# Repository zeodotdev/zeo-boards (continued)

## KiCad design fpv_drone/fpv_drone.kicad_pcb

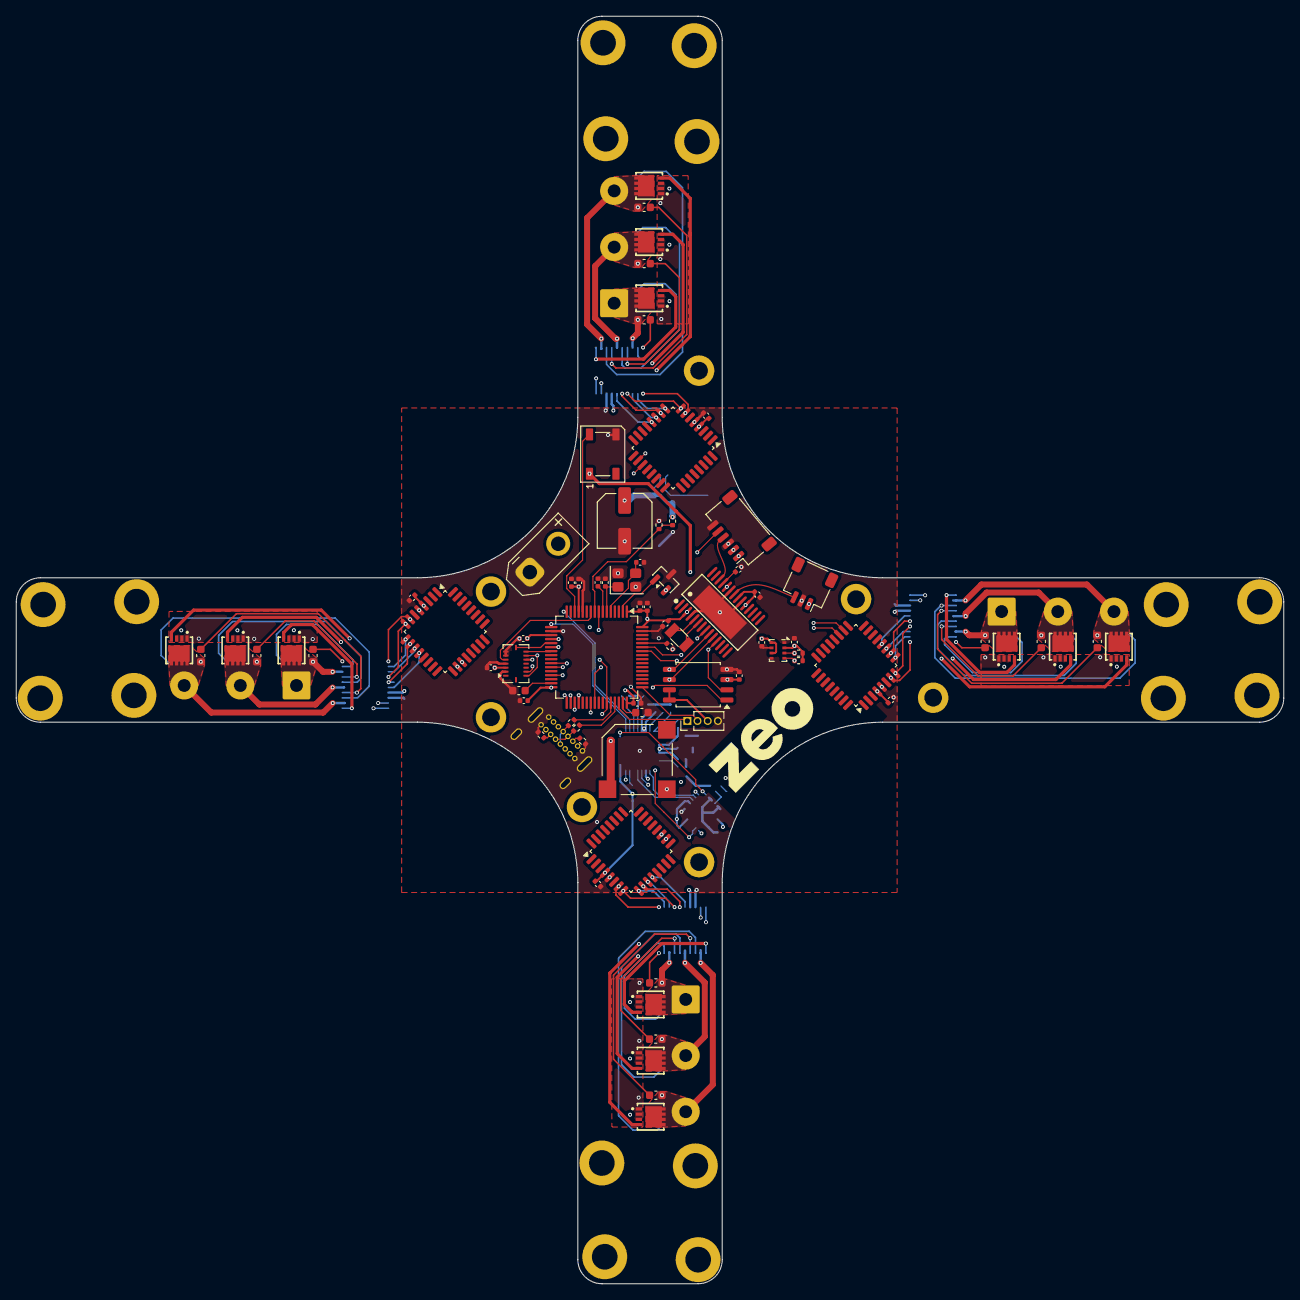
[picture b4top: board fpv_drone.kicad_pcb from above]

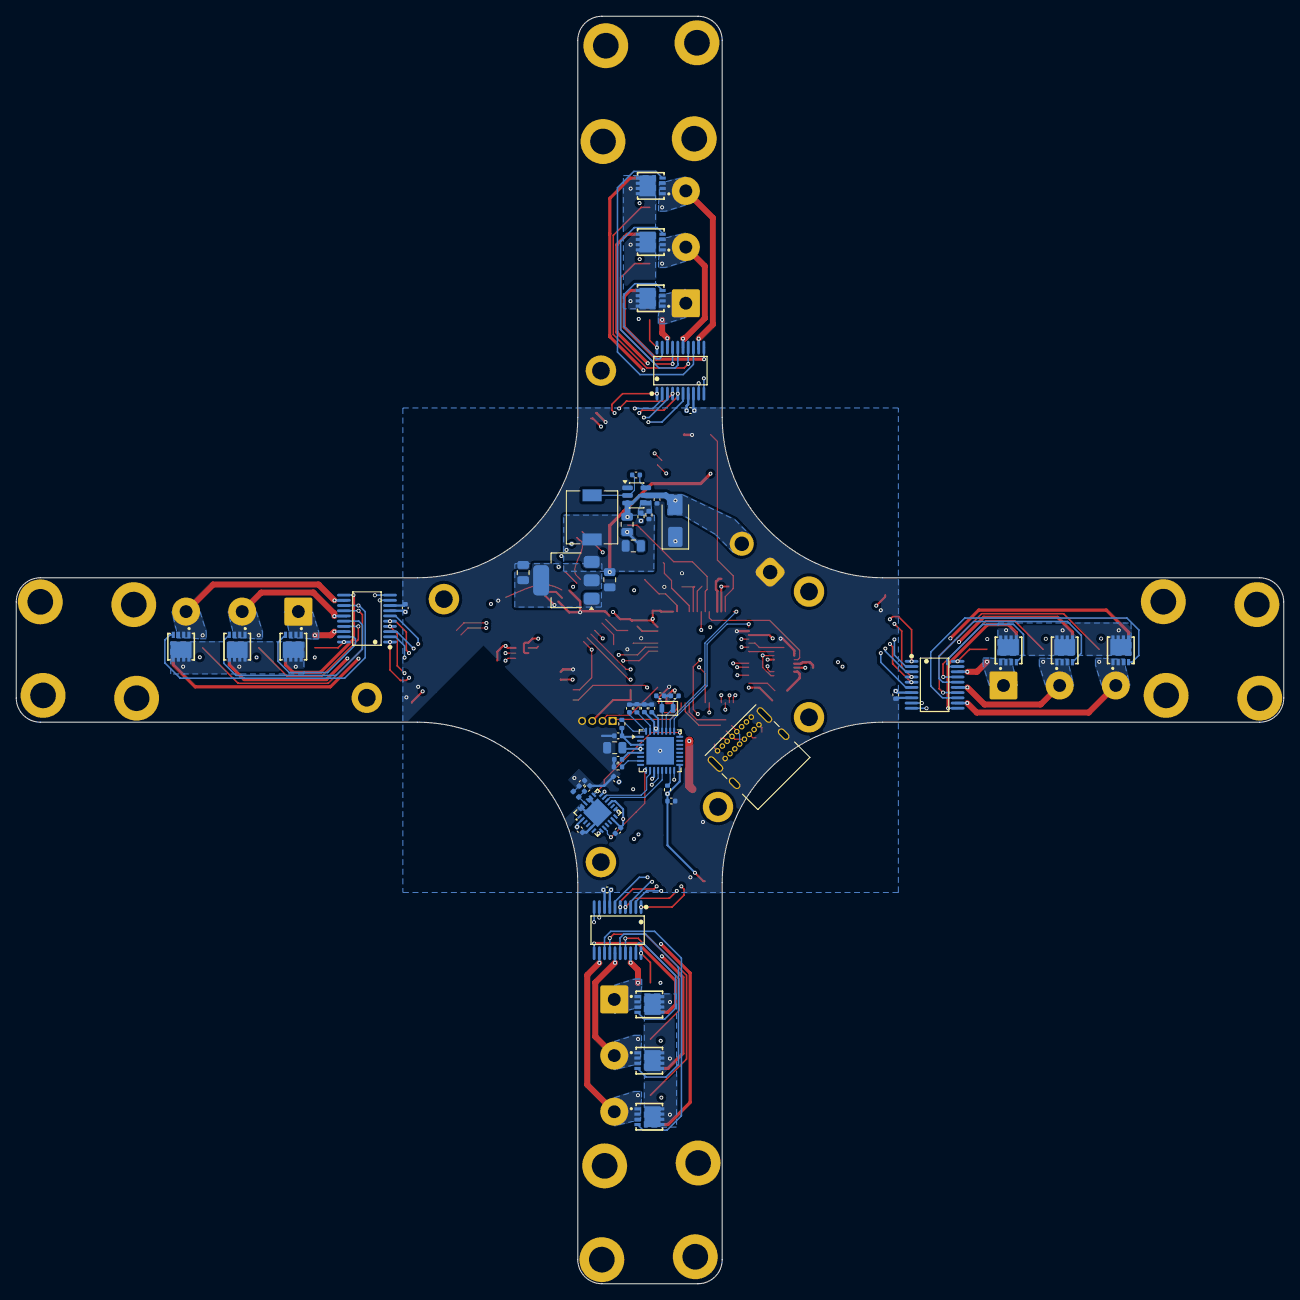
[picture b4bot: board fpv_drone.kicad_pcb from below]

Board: 6 copper layers, 158.0 x 158.0 mm, 134 parts (55 on the bottom side), 135 nets.

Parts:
C1, C60: DNP; C_0402_1005Metric
C2: 470µF/25V; C_Elec_6.3x5.8
C3, C11, C58: 10µF; C_0805_2012Metric
C4, C5, C6, C7, C8, C13, C14, C15, C19, C20, C21, C22, C23, C24, C25, C28, C31, C32, C33, C34, C38, C39, C43, C44, C48, C49, C53, C54, C55, C56, C57, C59: 100nF; C_0402_1005Metric
C9, C12: 22µF; C_0805_2012Metric
C10, C18: 1µF; C_0402_1005Metric
C16, C17: 10pF; C_0402_1005Metric
C26, C27: 20pF; C_0402_1005Metric
C29, C30: 2.2µF; C_0603_1608Metric
C35, C36, C37, C40, C41, C42, C45, C46, C47, C50, C51, C52: 100nF; C_0603_1608Metric
D2: SMBJ20A; D_SMA
D3: WS2812B; LED_WS2812B_PLCC4_5.0x5.0mm_P3.2mm
J2: BATT; AMASS_XT30UPB-M_1x02_P5.0mm_Vertical
J4: CAM; JST_SH_SM03B-SRSS-TB_1x03-1MP_P1.00mm_Horizontal
J5: VTX_MODULE; JST_SH_SM06B-SRSS-TB_1x06-1MP_P1.00mm_Horizontal
J6: USB-C; USB_C_Receptacle_GCT_USB4085
J7: MOT1; SolderWire-0.75sqmm_1x03_P7mm_D1.25mm_OD3.5mm
J8, J9, J10: MOT3; SolderWire-0.75sqmm_1x03_P7mm_D1.25mm_OD3.5mm
J11: BUZZER; MagneticBuzzer_Kobitone_254-EMB84Q-RO
J12: SWD_DEBUG; PinHeader_1x04_P1.27mm_Vertical
L1: 1.5nH; L_0402_1005Metric
L2: 4.7µH; L_6.3x6.3_H3
Q1, Q2, Q3, Q4, Q5, Q6, Q7, Q8, Q9, Q10, Q11, Q12, Q13, Q14, Q15, Q16, Q17, Q18, Q19, Q20, Q21, Q22, Q23, Q24: AON7418; PDFN-8_L3.3-W3.3-P0.65-BL
Q26: BSS138; SOT-23
R2: 73.2k; R_0402_1005Metric
R3, R7, R8, R9, R10: 10k; R_0402_1005Metric
R6: 12k; R_0402_1005Metric
R11, R12: 5.1k; R_0402_1005Metric
R13, R14: 22; R_0402_1005Metric
R15, R16: 100k; R_0402_1005Metric
R17, R18: 4.7k; R_0402_1005Metric
U2: TPS54302_5V; SOT-23-6
U4: AMS1117-3.3; SOT-223-3_TabPin2
U5: SX1280; QFN-24_L4.0-W4.0-P0.50-BL-EP2.6
U6: ESP8266EX; QFN-32-1EP_5x5mm_P0.5mm_EP3.45x3.45mm
U7: AT7456E; TSSOP-28_L9.7-W4.4-P0.65-LS6.4-BL-EP-2
U8: STM32F405RGTx; LQFP-64_10x10mm_P0.5mm
U9: STM32G071K_ESC1; LQFP-32_7x7mm_P0.8mm
U10: FD6288_ESC1; TSSOP-20_L6.5-W4.4-P0.65-LS6.4-BL
U11: STM32G071K_ESC3; LQFP-32_7x7mm_P0.8mm
U12: FD6288_ESC3; TSSOP-20_L6.5-W4.4-P0.65-LS6.4-BL
U13: STM32G071K_ESC2; LQFP-32_7x7mm_P0.8mm
U14: FD6288_ESC2; TSSOP-20_L6.5-W4.4-P0.65-LS6.4-BL
U15: STM32G071K_ESC4; LQFP-32_7x7mm_P0.8mm
U16: FD6288_ESC4; TSSOP-20_L6.5-W4.4-P0.65-LS6.4-BL
U17: BMI088; Bosch_LGA-16_4.5x3mm_P0.5mm_LayoutBorder7x1y_ClockwisePinNu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
U18: BMP280; Bosch_LGA-8_2x2.5mm_P0.65mm_ClockwisePinNumbering
U19: W25Q128JVS; SOIC-8_5.3x5.3mm_P1.27mm
Y2: 26MHz; Crystal_SMD_2012-2Pin_2.0x1.2mm
Y3: 27MHz; Crystal_SMD_3215-2Pin_3.2x1.5mm
Y4: 8MHz; Crystal_SMD_3225-4Pin_3.2x2.5mm

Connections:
+3V3: C5.2, C6.2, C7.2, C10.2, C12.2, C13.2, C14.2, C15.2, C19.2, C20.2, C21.2, C22.2, C23.2, C25.2, C31.2, C32.2, C33.2, C38.2, C43.2, C48.2, C53.1, C54.2, C55.2, C56.2, C57.2, C58.2, C59.2, J12.3, R7.2, R9.2, R17.2, R18.2, U4.2 (VO), U5.2 (VDD_IN), U5.11 (VBAT_IO), U5.15 (VBAT), U6.1 (VDDA), U6.3 (VDD3P3), U6.4 (VDD3P3), U6.5 (VDD_RTC), U6.11 (VDDPST), U6.17 (VDDPST), U6.29 (VDDD), U6.30 (VDDA), U7.3 (DVDD), U7.19 (RESET#), U7.21 (AVDD), U8.1 (VBAT), U8.13 (VDDA), U8.19 (VDD), U8.32 (VDD), U8.48 (VDD), U8.64 (VDD), U9.4 (VDD), U11.4 (VDD), U13.4 (VDD), U15.4 (VDD), U17.3 (VDD), U17.11 (VDDIO), U18.2 (CSB), U18.6 (VDDIO), U18.8 (VDD), U19.3 (~WP/IO_{2}), U19.7 (~HOLD/~RESET/IO_{3}), U19.8 (VCC)
+5V: C9.2, C11.2, D3.1 (VDD), J4.1, J5.1, J5.2, J11.1, L2.1, R2.2, U4.3 (VI), U7.24 (PVDD)
+BATT: C2.1, C3.2, C4.1, C34.2, C39.2, C44.2, C49.2, D2.2 (A2), J2.2, Q1.5 (D), Q1.6 (D), Q1.7 (D), Q1.8 (D), Q1.9 (D), Q3.5 (D), Q3.6 (D), Q3.7 (D), Q3.8 (D), Q3.9 (D), Q5.5 (D), Q5.6 (D), Q5.7 (D), Q5.8 (D), Q5.9 (D), Q7.5 (D), Q7.6 (D), Q7.7 (D), Q7.8 (D), Q7.9 (D), Q9.5 (D), Q9.6 (D), Q9.7 (D), Q9.8 (D), Q9.9 (D), Q11.5 (D), Q11.6 (D), Q11.7 (D), Q11.8 (D), Q11.9 (D), Q13.5 (D), Q13.6 (D), Q13.7 (D), Q13.8 (D), Q13.9 (D), Q15.5 (D), Q15.6 (D), Q15.7 (D), Q15.8 (D), Q15.9 (D), Q17.5 (D), Q17.6 (D), Q17.7 (D), Q17.8 (D), Q17.9 (D), Q19.5 (D), Q19.6 (D), Q19.7 (D), Q19.8 (D), Q19.9 (D), Q21.5 (D), Q21.6 (D), Q21.7 (D), Q21.8 (D), Q21.9 (D), Q23.5 (D), Q23.6 (D), Q23.7 (D), Q23.8 (D), Q23.9 (D), R15.1, U2.3 (VIN), U2.5 (EN), U10.7 (VCC), U12.7 (VCC), U14.7 (VCC), U16.7 (VCC)
/BARO_SCL: R17.1, U8.58 (PB6), U18.4 (SCK)
/BARO_SDA: R18.1, U8.59 (PB7), U18.3 (SDI)
/BUZZER: Q26.1 (G), U8.2 (PC13)
/ELRS Receiver/SX_BUSY: U5.7 (BUSY), U6.16 (GPIO4)
/ELRS Receiver/SX_DIO1: U5.8 (DIO1), U6.9 (MTMS)
/ELRS Receiver/SX_MISO: U5.16 (MISO_TX), U6.13 (MTDO)
/ELRS Receiver/SX_MOSI: U5.17 (MOSI_RX), U6.10 (MTDI)
/ELRS Receiver/SX_NSS: U5.19 (NSS_CTS), U6.24 (GPIO5)
/ELRS Receiver/SX_SCK: U5.18 (SCK_RTSN), U6.12 (MTCK)
/ELRS_RX: U6.25 (U0RXD), U8.17 (PA3)
/ELRS_TX: U6.26 (U0TXD), U8.16 (PA2)
/ESC/Motor 1/HIN1: U9.7 (PA0), U10.1 (HIN1)
/ESC/Motor 1/HIN2: U9.9 (PA2), U10.2 (HIN2)
/ESC/Motor 1/HIN3: U9.11 (PA4), U10.3 (HIN3)
/ESC/Motor 1/HO1: Q1.4 (G), U10.19 (HO1)
/ESC/Motor 1/HO2: Q3.4 (G), U10.16 (HO2)
/ESC/Motor 1/HO3: Q5.4 (G), U10.13 (HO3)
/ESC/Motor 1/LIN1: U9.8 (PA1), U10.4 (LIN1)
/ESC/Motor 1/LIN2: U9.10 (PA3), U10.5 (LIN2)
/ESC/Motor 1/LIN3: U9.12 (PA5), U10.6 (LIN3)
/ESC/Motor 1/LO1: Q2.4 (G), U10.11 (LO1)
/ESC/Motor 1/LO2: Q4.4 (G), U10.10 (LO2)
/ESC/Motor 1/LO3: Q6.4 (G), U10.9 (LO3)
/ESC/Motor 1/VB1: C35.1, U10.20 (VB1)
/ESC/Motor 1/VB2: C36.1, U10.17 (VB2)
/ESC/Motor 1/VB3: C37.1, U10.14 (VB3)
/ESC/Motor 1/VS1: C35.2, J7.1, Q1.1 (S), Q1.2 (S), Q1.3 (S), Q2.5 (D), Q2.6 (D), Q2.7 (D), Q2.8 (D), Q2.9 (D), U10.18 (VS1)
/ESC/Motor 1/VS2: C36.2, J7.2, Q3.1 (S), Q3.2 (S), Q3.3 (S), Q4.5 (D), Q4.6 (D), Q4.7 (D), Q4.8 (D), Q4.9 (D), U10.15 (VS2)
/ESC/Motor 1/VS3: C37.2, J7.3, Q5.1 (S), Q5.2 (S), Q5.3 (S), Q6.5 (D), Q6.6 (D), Q6.7 (D), Q6.8 (D), Q6.9 (D), U10.12 (VS3)
/ESC/Motor 2/HIN1: U13.7 (PA0), U14.1 (HIN1)
/ESC/Motor 2/HIN2: U13.9 (PA2), U14.2 (HIN2)
/ESC/Motor 2/HIN3: U13.11 (PA4), U14.3 (HIN3)
/ESC/Motor 2/HO1: Q13.4 (G), U14.19 (HO1)
/ESC/Motor 2/HO2: Q15.4 (G), U14.16 (HO2)
/ESC/Motor 2/HO3: Q17.4 (G), U14.13 (HO3)
/ESC/Motor 2/LIN1: U13.8 (PA1), U14.4 (LIN1)
/ESC/Motor 2/LIN2: U13.10 (PA3), U14.5 (LIN2)
/ESC/Motor 2/LIN3: U13.12 (PA5), U14.6 (LIN3)
/ESC/Motor 2/LO1: Q14.4 (G), U14.11 (LO1)
/ESC/Motor 2/LO2: Q16.4 (G), U14.10 (LO2)
/ESC/Motor 2/LO3: Q18.4 (G), U14.9 (LO3)
/ESC/Motor 2/VB1: C45.1, U14.20 (VB1)
/ESC/Motor 2/VB2: C46.1, U14.17 (VB2)
/ESC/Motor 2/VB3: C47.1, U14.14 (VB3)
/ESC/Motor 2/VS1: C45.2, J9.1, Q13.1 (S), Q13.2 (S), Q13.3 (S), Q14.5 (D), Q14.6 (D), Q14.7 (D), Q14.8 (D), Q14.9 (D), U14.18 (VS1)
/ESC/Motor 2/VS2: C46.2, J9.2, Q15.1 (S), Q15.2 (S), Q15.3 (S), Q16.5 (D), Q16.6 (D), Q16.7 (D), Q16.8 (D), Q16.9 (D), U14.15 (VS2)
/ESC/Motor 2/VS3: C47.2, J9.3, Q17.1 (S), Q17.2 (S), Q17.3 (S), Q18.5 (D), Q18.6 (D), Q18.7 (D), Q18.8 (D), Q18.9 (D), U14.12 (VS3)
/ESC/Motor 3/HIN1: U11.7 (PA0), U12.1 (HIN1)
/ESC/Motor 3/HIN2: U11.9 (PA2), U12.2 (HIN2)
/ESC/Motor 3/HIN3: U11.11 (PA4), U12.3 (HIN3)
/ESC/Motor 3/HO1: Q7.4 (G), U12.19 (HO1)
/ESC/Motor 3/HO2: Q9.4 (G), U12.16 (HO2)
/ESC/Motor 3/HO3: Q11.4 (G), U12.13 (HO3)
/ESC/Motor 3/LIN1: U11.8 (PA1), U12.4 (LIN1)
/ESC/Motor 3/LIN2: U11.10 (PA3), U12.5 (LIN2)
/ESC/Motor 3/LIN3: U11.12 (PA5), U12.6 (LIN3)
/ESC/Motor 3/LO1: Q8.4 (G), U12.11 (LO1)
/ESC/Motor 3/LO2: Q10.4 (G), U12.10 (LO2)
/ESC/Motor 3/LO3: Q12.4 (G), U12.9 (LO3)
/ESC/Motor 3/VB1: C40.1, U12.20 (VB1)
/ESC/Motor 3/VB2: C41.1, U12.17 (VB2)
/ESC/Motor 3/VB3: C42.1, U12.14 (VB3)
/ESC/Motor 3/VS1: C40.2, J8.1, Q7.1 (S), Q7.2 (S), Q7.3 (S), Q8.5 (D), Q8.6 (D), Q8.7 (D), Q8.8 (D), Q8.9 (D), U12.18 (VS1)
/ESC/Motor 3/VS2: C41.2, J8.2, Q9.1 (S), Q9.2 (S), Q9.3 (S), Q10.5 (D), Q10.6 (D), Q10.7 (D), Q10.8 (D), Q10.9 (D), U12.15 (VS2)
/ESC/Motor 3/VS3: C42.2, J8.3, Q11.1 (S), Q11.2 (S), Q11.3 (S), Q12.5 (D), Q12.6 (D), Q12.7 (D), Q12.8 (D), Q12.9 (D), U12.12 (VS3)
/ESC/Motor 4/HIN1: U15.7 (PA0), U16.1 (HIN1)
/ESC/Motor 4/HIN2: U15.9 (PA2), U16.2 (HIN2)
/ESC/Motor 4/HIN3: U15.11 (PA4), U16.3 (HIN3)
/ESC/Motor 4/HO1: Q19.4 (G), U16.19 (HO1)
/ESC/Motor 4/HO2: Q21.4 (G), U16.16 (HO2)
/ESC/Motor 4/HO3: Q23.4 (G), U16.13 (HO3)
/ESC/Motor 4/LIN1: U15.8 (PA1), U16.4 (LIN1)
/ESC/Motor 4/LIN2: U15.10 (PA3), U16.5 (LIN2)
/ESC/Motor 4/LIN3: U15.12 (PA5), U16.6 (LIN3)
/ESC/Motor 4/LO1: Q20.4 (G), U16.11 (LO1)
/ESC/Motor 4/LO2: Q22.4 (G), U16.10 (LO2)
/ESC/Motor 4/LO3: Q24.4 (G), U16.9 (LO3)
/ESC/Motor 4/VB1: C50.1, U16.20 (VB1)
/ESC/Motor 4/VB2: C51.1, U16.17 (VB2)
/ESC/Motor 4/VB3: C52.1, U16.14 (VB3)
/ESC/Motor 4/VS1: C50.2, J10.1, Q19.1 (S), Q19.2 (S), Q19.3 (S), Q20.5 (D), Q20.6 (D), Q20.7 (D), Q20.8 (D), Q20.9 (D), U16.18 (VS1)
/ESC/Motor 4/VS2: C51.2, J10.2, Q21.1 (S), Q21.2 (S), Q21.3 (S), Q22.5 (D), Q22.6 (D), Q22.7 (D), Q22.8 (D), Q22.9 (D), U16.15 (VS2)
/ESC/Motor 4/VS3: C52.2, J10.3, Q23.1 (S), Q23.2 (S), Q23.3 (S), Q24.5 (D), Q24.6 (D), Q24.7 (D), Q24.8 (D), Q24.9 (D), U16.12 (VS3)
/ESC_RX: U8.43 (PA10), U9.18 (PA8), U11.18 (PA8), U13.18 (PA8), U15.18 (PA8)
/FLASH_CS: U8.8 (PC0), U19.1 (~CS)
/Flight Controller/USB_DM: R13.1, U8.44 (PA11)
/Flight Controller/USB_DP: R14.1, U8.45 (PA12)
/IMU_ACC_CS: U8.10 (PC2), U17.5 (~CSB2)
/IMU_CS: U8.20 (PA4), U17.14 (~CSB1)
/IMU_MISO: U8.22 (PA6), U17.10 (SDO2), U17.15 (SDO1)
/IMU_MOSI: U8.23 (PA7), U17.9 (SDI/SDA)
/IMU_SCK: U8.21 (PA5), U17.8 (SCK/SCL)
/LED_DATA: D3.4 (DIN), U8.14 (PA0)
/MOT1_PWM: U8.26 (PB0), U9.19 (PA9/UCPD1_DBCC1)
/MOT2_PWM: U8.27 (PB1), U13.19 (PA9/UCPD1_DBCC1)
/MOT3_PWM: U8.39 (PC8), U11.19 (PA9/UCPD1_DBCC1)
/MOT4_PWM: U8.40 (PC9), U15.19 (PA9/UCPD1_DBCC1)
/OSD and VTX/VID_IN: J4.3, U7.22 (VIN)
/OSD and VTX/VID_OUT: J5.4, U7.26 (VOUT)
/OSD_CS: U7.8 (CS#), U8.33 (PB12)
/Power Supply/FB_5V: R2.1, R3.2, U2.4 (FB)
/Power Supply/SW_5V: C8.2, L2.2, U2.2 (SW)
/SPI2_MISO: U7.11 (SDOUT), U8.35 (PB14), U19.2 (DO/IO_{1})
/SPI2_MOSI: U7.9 (SDIN), U8.36 (PB15), U19.5 (DI/IO_{0})
/SPI2_SCK: U7.10 (SCLK), U8.34 (PB13), U19.6 (CLK)
/SWCLK: J12.2, U8.49 (PA14)
/SWDIO: J12.1, U8.46 (PA13)
/VBAT_SENSE: R15.2, R16.1, U8.9 (PC1)
/VTX_SA: J5.5, U8.29 (PB10)
GND: C1.2, C2.2, C3.1, C4.2, C5.1, C6.1, C7.1, C9.1, C10.1, C11.1, C12.1, C13.1, C14.1, C15.1, C16.1, C17.2, C18.1, C19.1, C20.1, C21.1, C22.1, C23.1, C24.2, C25.1, C26.2, C27.1, C28.1, C29.1, C30.1, C31.1, C32.1, C33.1, C34.1, C38.1, C39.1, C43.1, C44.1, C48.1, C49.1, C53.2, C54.1, C55.1, C56.1, C57.1, C58.1, C59.1, C60.1, C60.2, D2.1 (A1), D3.3 (VSS), J2.1, J4.2, J5.3, J5.6, J6.A1 (GND), J6.A12 (GND), J6.B1 (GND), J6.B12 (GND), J6.S1 (SHIELD), J12.4, L1.2, Q2.1 (S), Q2.2 (S), Q2.3 (S), Q4.1 (S), Q4.2 (S), Q4.3 (S), Q6.1 (S), Q6.2 (S), Q6.3 (S), Q8.1 (S), Q8.2 (S), Q8.3 (S), Q10.1 (S), Q10.2 (S), Q10.3 (S), Q12.1 (S), Q12.2 (S), Q12.3 (S), Q14.1 (S), Q14.2 (S), Q14.3 (S), Q16.1 (S), Q16.2 (S), Q16.3 (S), Q18.1 (S), Q18.2 (S), Q18.3 (S), Q20.1 (S), Q20.2 (S), Q20.3 (S), Q22.1 (S), Q22.2 (S), Q22.3 (S), Q24.1 (S), Q24.2 (S), Q24.3 (S), Q26.3 (S), R3.1, R6.1, R8.2, R10.1, R11.1, R12.1, R16.2, U2.1 (GND), U4.1 (GND), U5.5 (GND), U5.13 (GND), U5.20 (GND), U5.21 (GND), U5.23 (GND), U5.24 (GND), U5.25 (GND), U6.33 (GND), U7.4 (DGND), U7.20 (AGND), U7.23 (PGND), U7.29 (EP), U8.12 (VSSA), U8.18 (VSS), U8.63 (VSS), U9.5 (VSS), U10.8 (COM), U11.5 (VSS), U12.8 (COM), U13.5 (VSS), U14.8 (COM), U15.5 (VSS), U16.8 (COM), U17.2 (GNDA), U17.4 (GNDA), U17.6 (GNDIO), U17.7 (PS), U18.1 (GND), U18.5 (SDO), U18.7 (GND), U19.4 (GND), Y4.2 (G), Y4.4 (G)
unnamed: J6.A5 (CC1), R11.2
unnamed: J6.B5 (CC2), R12.2
unnamed: J6.A6 (D+), J6.B6 (D+), R14.2
unnamed: J6.A7 (D-), J6.B7 (D-), R13.2
unnamed: J11.2, Q26.2 (D)
unnamed: C8.1, U2.6 (BOOT)
unnamed: C1.1, L1.1, U5.22 (RFIO)
unnamed: R8.1, U6.7 (CHIP_PU)
unnamed: R9.1, U6.15 (GPIO0)
unnamed: R6.2, U6.31 (RES12K)
unnamed: C17.1, U6.28 (XTAL_IN), Y2.2
unnamed: C16.2, U6.27 (XTAL_OUT), Y2.1
unnamed: C18.2, R7.1, U6.32 (~EXT_RSTB)
unnamed: U7.5 (CLKIN), Y3.2
unnamed: C24.1, U7.25 (SAG)
unnamed: U7.6 (XFB), Y3.1
unnamed: R10.2, U8.60 (BOOT0)
unnamed: C28.2, U8.7 (NRST)
unnamed: C26.1, U8.5 (PH0), Y4.3
unnamed: C27.2, U8.6 (PH1), Y4.1
unnamed: C29.2, U8.31 (VCAP_1)
unnamed: C30.2, U8.47 (VCAP_2)

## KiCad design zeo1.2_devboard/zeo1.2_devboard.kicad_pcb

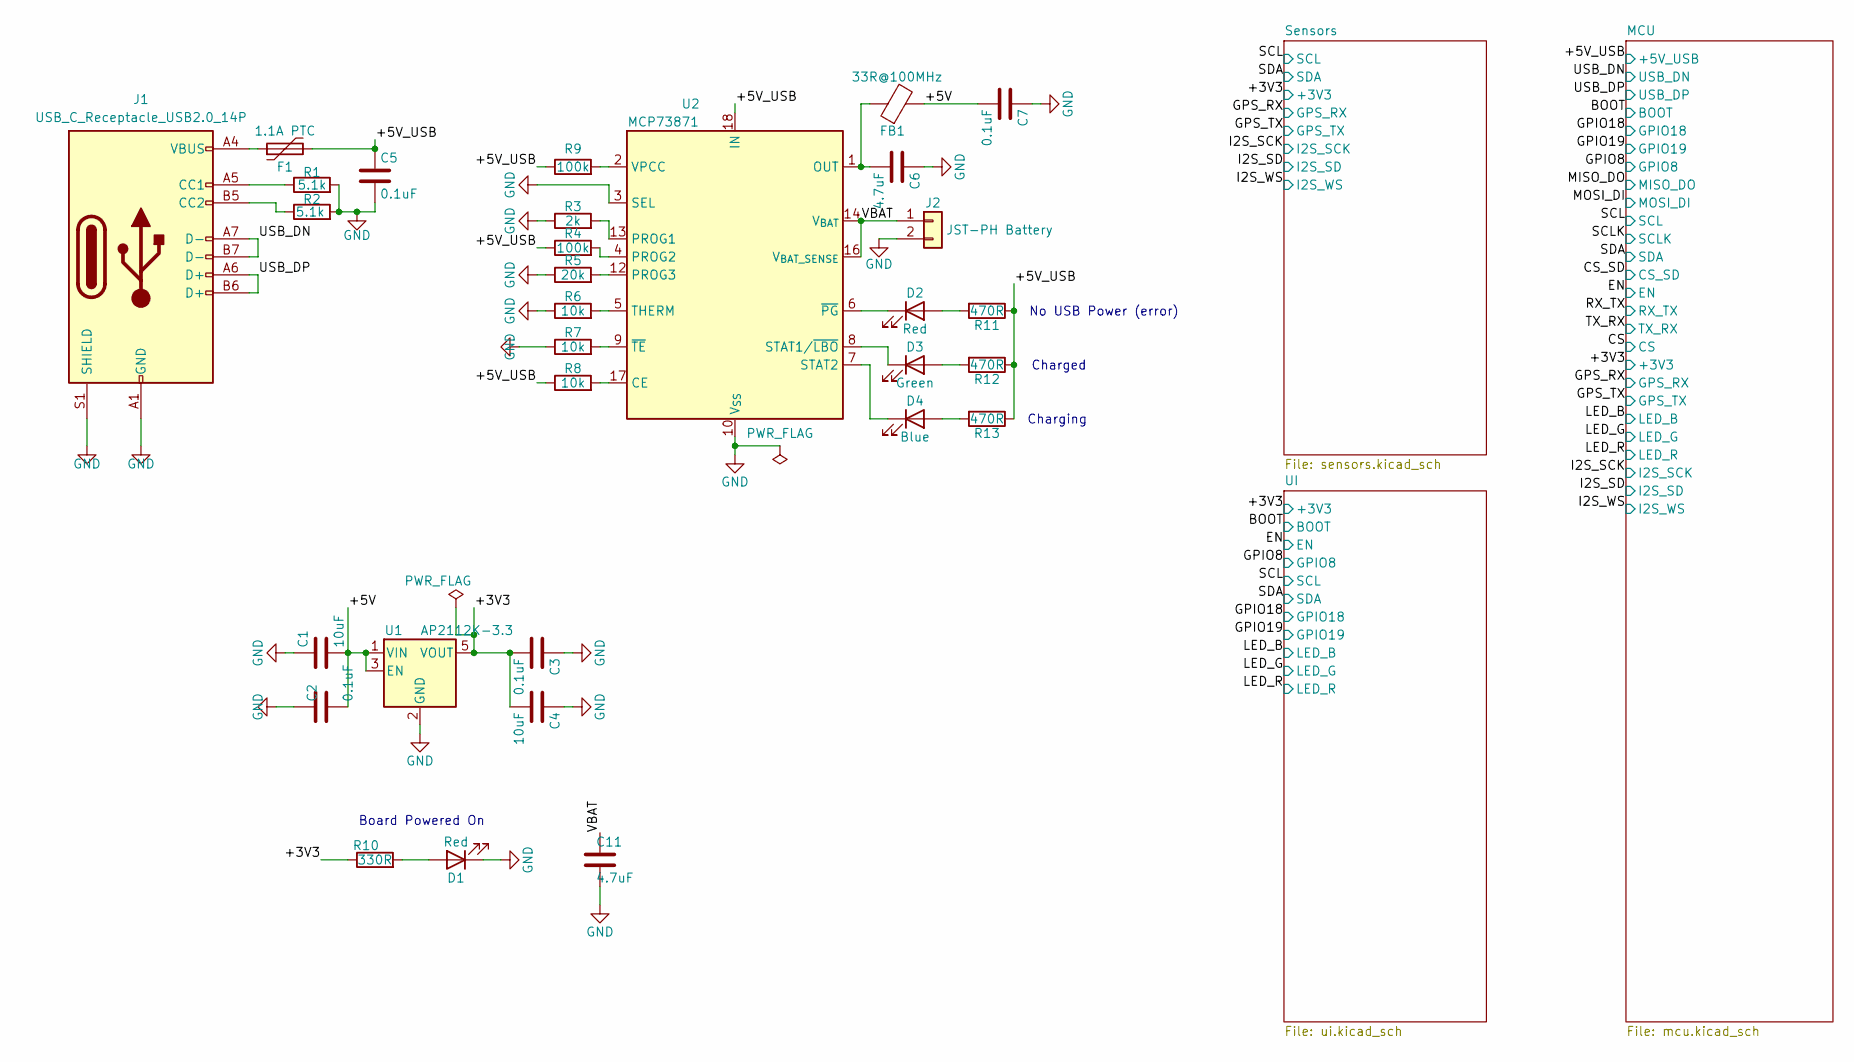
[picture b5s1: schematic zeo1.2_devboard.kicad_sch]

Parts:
C1, C4: 10uF; C_0805_2012Metric
C2, C3, C5, C7: 0.1uF; C_0402_1005Metric
C6: 4.7uF; C_0402_1005Metric
C11: 4.7uF; C_0805_2012Metric
D1, D2: Red; LED_0402_1005Metric
D3: Green; LED_0402_1005Metric
D4: Blue; LED_0402_1005Metric
F1: 1.1A PTC; Fuse_0402_1005Metric
FB1: 33R@100MHz; L_0402_1005Metric
J1: USB_C_Receptacle_USB2.0_14P; USB_C_Receptacle_GCT_USB4085
J2: JST-PH Battery; JST_PH_B2B-PH-K_1x02_P2.00mm_Vertical
R1, R2: 5.1k; R_0402_1005Metric
R3: 2k; R_0402_1005Metric
R4, R9: 100k; R_0402_1005Metric
R5: 20k; R_0402_1005Metric
R6, R7, R8: 10k; R_0402_1005Metric
R10: 330R; R_0402_1005Metric
R11, R12, R13: 470R; R_0402_1005Metric
U1: AP2112K-3.3; SOT-23-5
U2: MCP73871; QFN-20-1EP_4x4mm_P0.5mm_EP2.5x2.5mm

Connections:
+3V3: C3.2, C4.2, R10.1, U1.5 (VOUT); also elsewhere on the board
/+5V: C1.2, C2.2, C7.2, FB1.2, U1.1 (VIN), U1.3 (EN)
/+5V_USB: C5.1, F1.2, R4.1, R8.1, R9.1, R11.1, R12.1, R13.1, U2.18 (IN), U2.19 (IN); also elsewhere on the board
/USB_DN: J1.A7 (D-), J1.B7 (D-); also elsewhere on the board
/USB_DP: J1.A6 (D+), J1.B6 (D+); also elsewhere on the board
/VBAT: C11.1, J2.1, U2.14 (V_{BAT}), U2.15 (V_{BAT}), U2.16 (V_{BAT_SENSE})
GND: C1.1, C2.1, C3.1, C4.1, C5.2, C6.1, C7.1, C11.2, D1.1 (K), J1.A1 (GND), J1.A12 (GND), J1.B1 (GND), J1.B12 (GND), J1.S1 (SHIELD), J2.2, R1.2, R2.2, R3.1, R5.1, R6.1, R7.1, U1.2 (GND), U2.3 (SEL), U2.10 (V_{SS}), U2.11 (V_{SS}), U2.21 (V_{SS}); also elsewhere on the board
unnamed: C6.2, FB1.1, U2.1 (OUT), U2.20 (OUT)
unnamed: D1.2 (A), R10.2
unnamed: D2.2 (A), R11.2
unnamed: D2.1 (K), U2.6 (~PG)
unnamed: D3.2 (A), R12.2
unnamed: D3.1 (K), U2.8 (STAT1/~LBO)
unnamed: D4.2 (A), R13.2
unnamed: D4.1 (K), U2.7 (STAT2)
unnamed: F1.1, J1.A4 (VBUS), J1.A9 (VBUS), J1.B4 (VBUS), J1.B9 (VBUS)
unnamed: J1.A5 (CC1), R1.1
unnamed: J1.B5 (CC2), R2.1
unnamed: R8.2, U2.17 (CE)
unnamed: R3.2, U2.13 (PROG1)
unnamed: R4.2, U2.4 (PROG2)
unnamed: R5.2, U2.12 (PROG3)
unnamed: R6.2, U2.5 (THERM)
unnamed: R9.2, U2.2 (VPCC)
unnamed: R7.2, U2.9 (~TE)

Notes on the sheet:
Charged
Board Powered On
Charging
No USB Power (error)

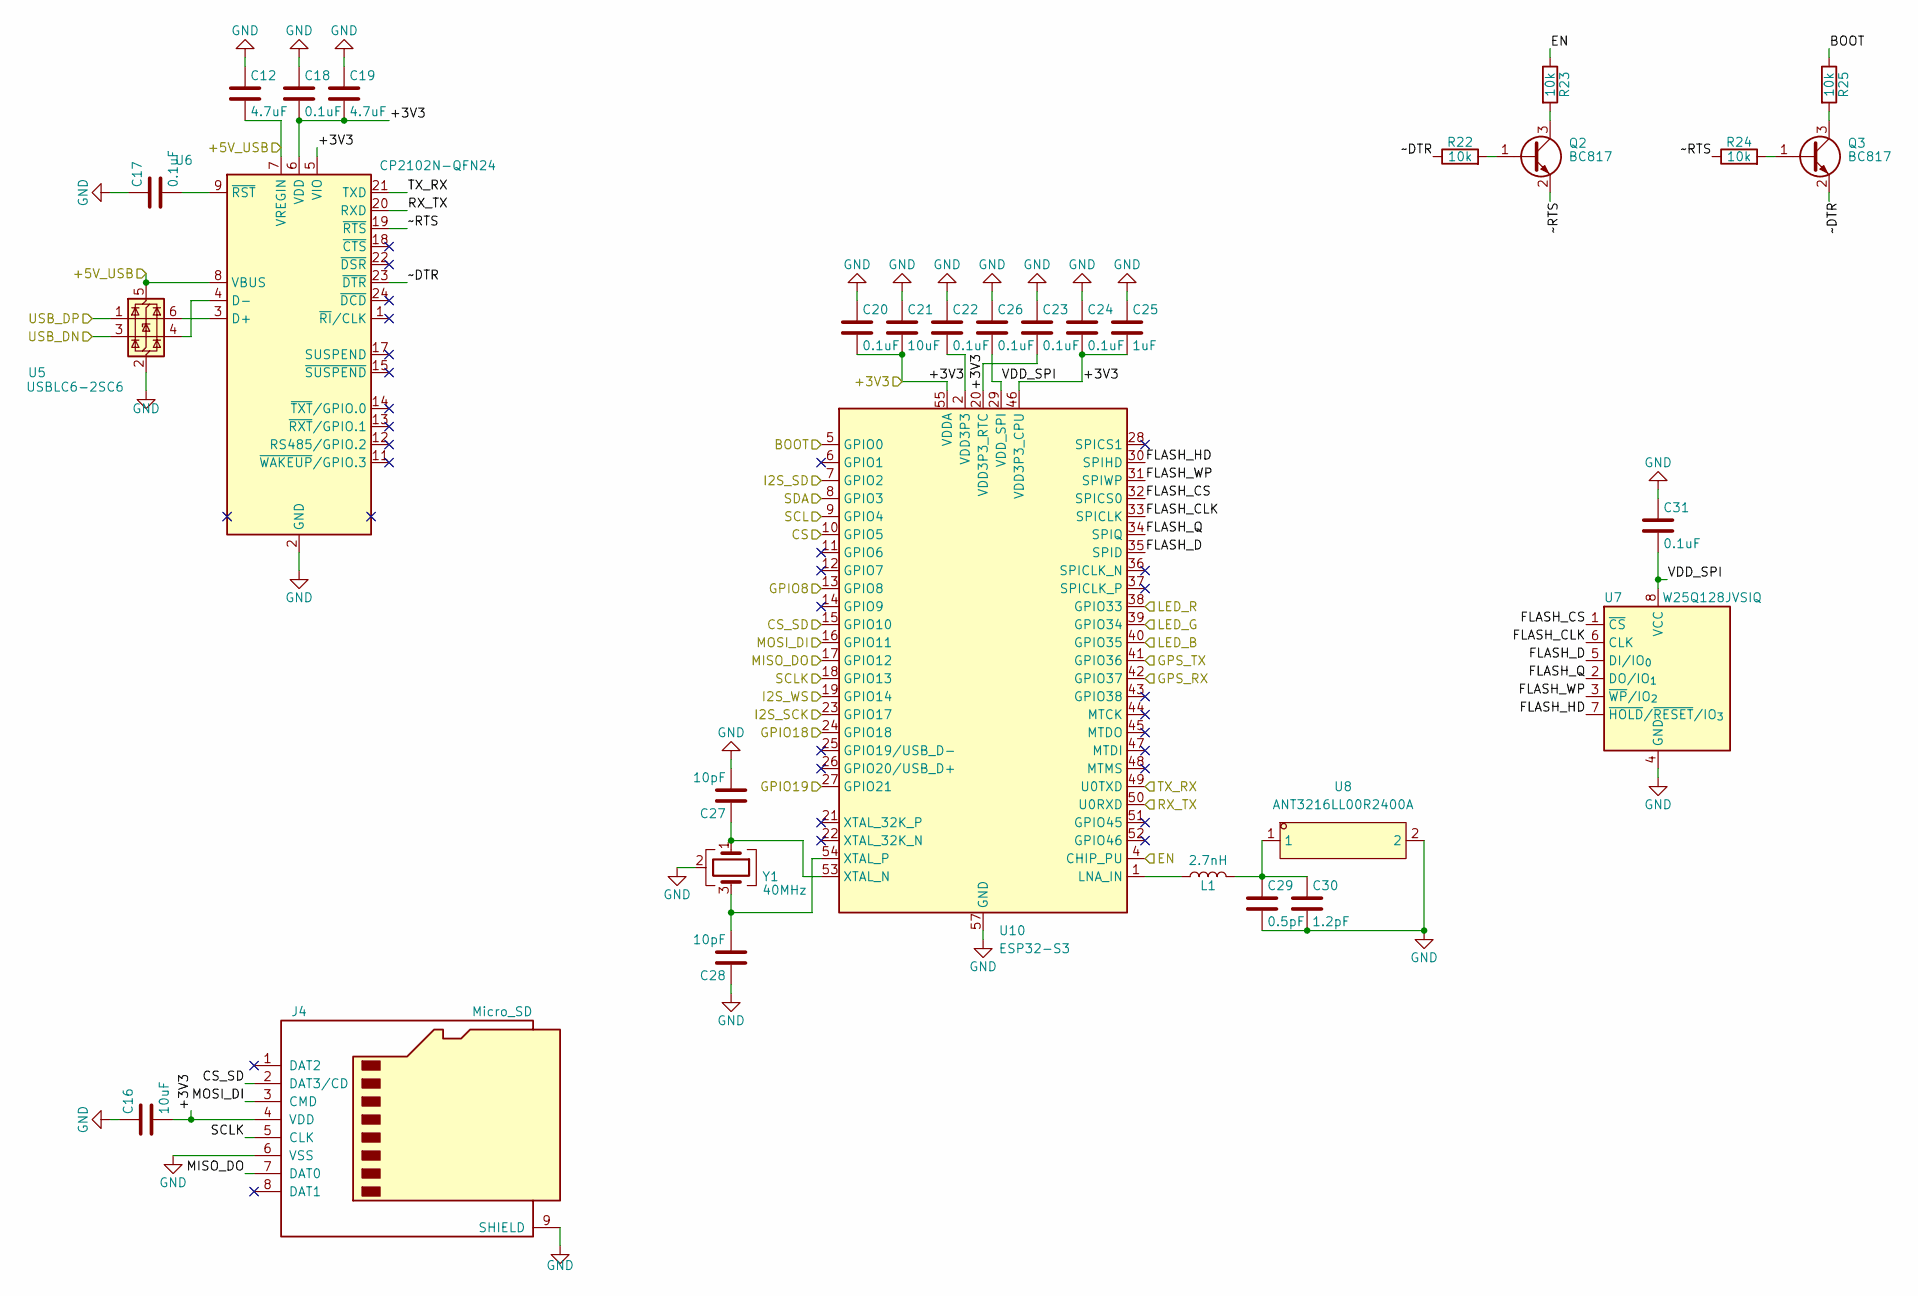
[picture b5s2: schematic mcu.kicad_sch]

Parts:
C12, C19: 4.7uF; C_0805_2012Metric
C16, C21: 10uF; C_0805_2012Metric
C17, C18, C20, C22, C23, C24, C26, C31: 0.1uF; C_0402_1005Metric
C25: 1uF; C_0402_1005Metric
C27, C28: 10pF; C_0402_1005Metric
C29: 0.5pF; C_0402_1005Metric
C30: 1.2pF; C_0402_1005Metric
J4: Micro_SD; microSD_HC_Hirose_DM3D-SF
L1: 2.7nH; L_0402_1005Metric
Q2, Q3: BC817; SOT-23
R22, R23, R24, R25: 10k; R_0402_1005Metric
U5: USBLC6-2SC6; SOT-23-6
U6: CP2102N-QFN24; QFN-24-1EP_4x4mm_P0.5mm_EP2.6x2.6mm
U7: W25Q128JVSIQ; SOIC-8_5.3x5.3mm_P1.27mm
U8: ANT3216LL00R2400A; ANT-SMD_L3.2-W1.6; LCSC Part C293767
U10: ESP32-S3; QFN-56-1EP_7x7mm_P0.4mm_EP4x4mm
Y1: 40MHz; Crystal_SMD_WE_IQXC-240-4Pin_1.2x1.0mm

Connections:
+3V3: C16.2, C18.2, C19.2, C20.2, C21.2, C22.2, C23.2, C24.2, C25.2, J4.4 (VDD), U6.5 (VIO), U6.6 (VDD), U10.2 (VDD3P3), U10.3 (VDD3P3), U10.20 (VDD3P3_RTC), U10.46 (VDD3P3_CPU), U10.55 (VDDA), U10.56 (VDDA); also elsewhere on the board
/+5V_USB: C12.2, U5.5 (VBUS), U6.7 (VREGIN), U6.8 (VBUS); also elsewhere on the board
/BOOT: R25.1, U10.5 (GPIO0); also elsewhere on the board
/CS: U10.10 (GPIO5)
/CS_SD: J4.2 (DAT3/CD), U10.15 (GPIO10)
/EN: R23.1, U10.4 (CHIP_PU); also elsewhere on the board
/GPIO8: U10.13 (GPIO8)
/GPIO18: U10.24 (GPIO18)
/GPIO19: U10.27 (GPIO21)
/GPS_RX: U10.42 (GPIO37); also elsewhere on the board
/GPS_TX: U10.41 (GPIO36); also elsewhere on the board
/I2S_SCK: U10.23 (GPIO17); also elsewhere on the board
/I2S_SD: U10.7 (GPIO2); also elsewhere on the board
/I2S_WS: U10.19 (GPIO14); also elsewhere on the board
/LED_B: U10.40 (GPIO35); also elsewhere on the board
/LED_G: U10.39 (GPIO34); also elsewhere on the board
/LED_R: U10.38 (GPIO33); also elsewhere on the board
/MCU/FLASH_CLK: U7.6 (CLK), U10.33 (SPICLK)
/MCU/FLASH_CS: U7.1 (~CS), U10.32 (SPICS0)
/MCU/FLASH_D: U7.5 (DI/IO_{0}), U10.35 (SPID)
/MCU/FLASH_HD: U7.7 (~HOLD/~RESET/IO_{3}), U10.30 (SPIHD)
/MCU/FLASH_Q: U7.2 (DO/IO_{1}), U10.34 (SPIQ)
/MCU/FLASH_WP: U7.3 (~WP/IO_{2}), U10.31 (SPIWP)
/MCU/VDD_SPI: C26.2, C31.2, U7.8 (VCC), U10.29 (VDD_SPI)
/MCU/~DTR: Q3.2 (E), R22.1, U6.23 (~DTR)
/MCU/~RTS: Q2.2 (E), R24.1, U6.19 (~RTS)
/MISO_DO: J4.7 (DAT0), U10.17 (GPIO12)
/MOSI_DI: J4.3 (CMD), U10.16 (GPIO11)
/RX_TX: U6.20 (RXD), U10.50 (U0RXD)
/SCL: U10.9 (GPIO4); also elsewhere on the board
/SCLK: J4.5 (CLK), U10.18 (GPIO13)
/SDA: U10.8 (GPIO3); also elsewhere on the board
/TX_RX: U6.21 (TXD), U10.49 (U0TXD)
/USB_DN: U5.3 (I/O2); also elsewhere on the board
/USB_DP: U5.1 (I/O1); also elsewhere on the board
GND: C12.1, C16.1, C17.1, C18.1, C19.1, C20.1, C21.1, C22.1, C23.1, C24.1, C25.1, C26.1, C27.2, C28.1, C29.2, C30.2, C31.1, J4.6 (VSS), J4.9 (SHIELD), U5.2 (GND), U6.2 (GND), U6.25 (GND), U7.4 (GND), U8.2, U10.57 (GND), Y1.2 (G), Y1.4 (G); also elsewhere on the board
unnamed: C29.1, C30.1, L1.2, U8.1
unnamed: Q2.1 (B), R22.2
unnamed: Q2.3 (C), R23.2
unnamed: Q3.1 (B), R24.2
unnamed: Q3.3 (C), R25.2
unnamed: U5.6 (I/O1), U6.3 (D+)
unnamed: U5.4 (I/O2), U6.4 (D-)
unnamed: C17.2, U6.9 (~RST)
unnamed: L1.1, U10.1 (LNA_IN)
unnamed: C27.1, U10.53 (XTAL_N), Y1.1
unnamed: C28.2, U10.54 (XTAL_P), Y1.3

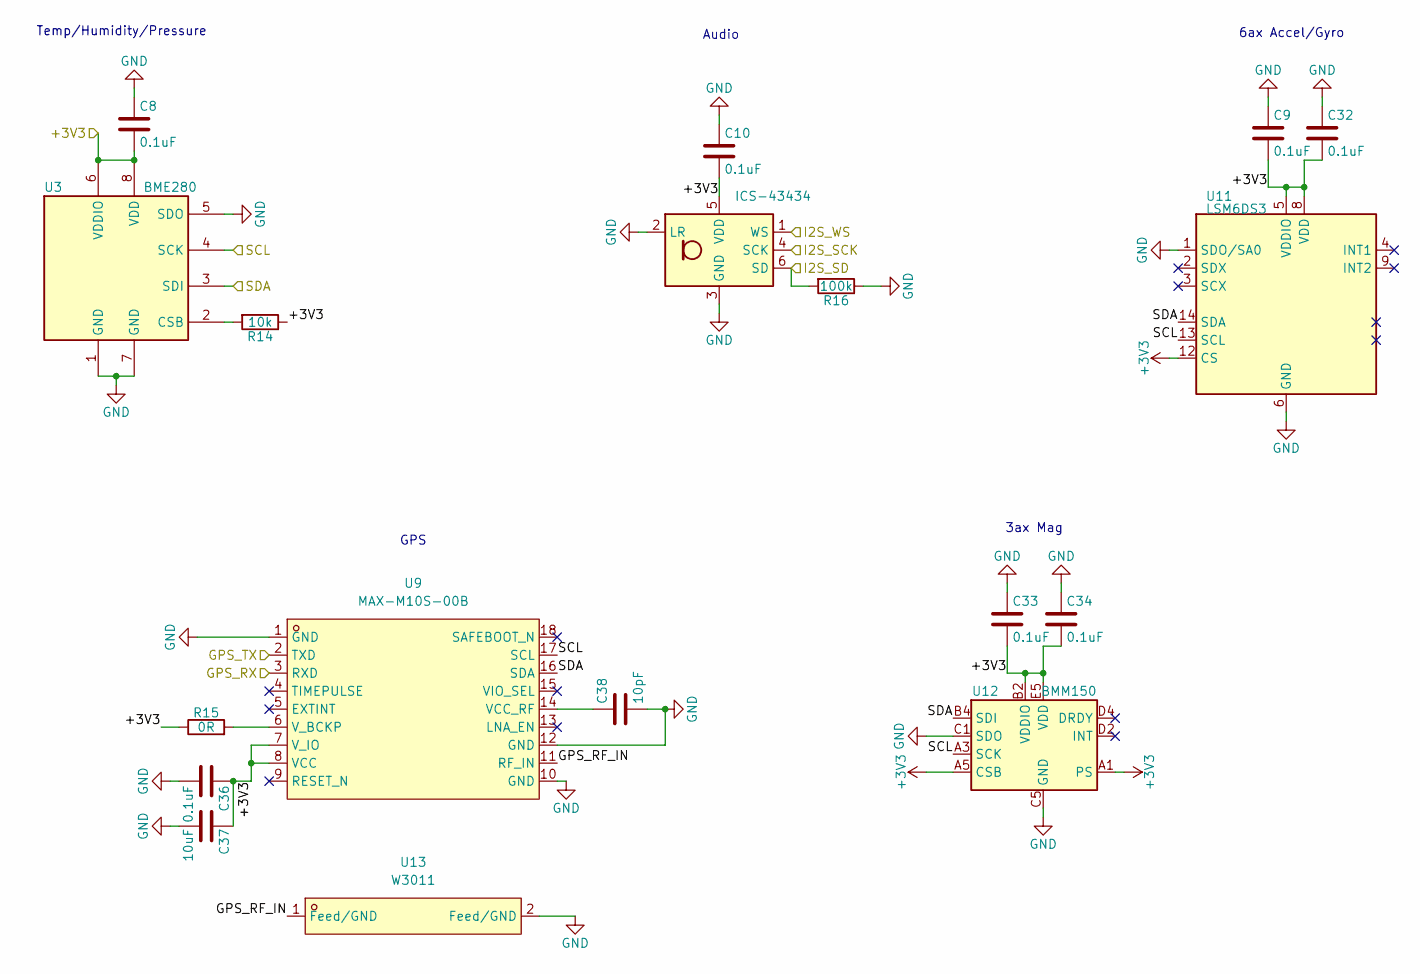
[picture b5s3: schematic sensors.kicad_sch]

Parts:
C8, C9, C10, C32, C33, C34, C36: 0.1uF; C_0402_1005Metric
C37: 10uF; C_0805_2012Metric
C38: 10pF; C_0402_1005Metric
MK2: ICS-43434; InvenSense_ICS-43434-6_3.5x2.65mm
R14: 10k; R_0402_1005Metric
R15: 0R; R_0402_1005Metric
R16: 100k; R_0402_1005Metric
U3: BME280; Bosch_LGA-8_2.5x2.5mm_P0.65mm_ClockwisePinNumbering
U9: MAX-M10S-00B; SMD-18_L10.1-W9.7-P1.10-TL_SKG09F; LCSC Part C4153167
U11: LSM6DS3; LGA-14_3x2.5mm_P0.5mm_LayoutBorder3x4y
U12: BMM150; WLCSP-12_1.56x1.56mm_P0.4mm
U13: W3011; ANT-SMD_L3.2-W1.6-2; LCSC Part C6604735

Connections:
+3V3: C8.2, C9.2, C10.2, C32.2, C33.2, C34.2, C36.1, C37.1, MK2.5 (VDD), R14.1, R15.1, U3.6 (VDDIO), U3.8 (VDD), U9.7 (V_IO), U9.8 (VCC), U11.5 (VDDIO), U11.8 (VDD), U11.12 (CS), U12.A1 (PS), U12.A5 (CSB), U12.B2 (VDDIO), U12.E5 (VDD); also elsewhere on the board
/GPS_RX: U9.3 (RXD); also elsewhere on the board
/GPS_TX: U9.2 (TXD); also elsewhere on the board
/I2S_SCK: MK2.4 (SCK); also elsewhere on the board
/I2S_SD: MK2.6 (SD), R16.2; also elsewhere on the board
/I2S_WS: MK2.1 (WS); also elsewhere on the board
/SCL: U3.4 (SCK), U9.17 (SCL), U11.13 (SCL), U12.A3 (SCK); also elsewhere on the board
/SDA: U3.3 (SDI), U9.16 (SDA), U11.14 (SDA), U12.B4 (SDI); also elsewhere on the board
/Sensors/GPS_RF_IN: U9.11 (RF_IN), U13.1 (Feed/GND)
GND: C8.1, C9.1, C10.1, C32.1, C33.1, C34.1, C36.2, C37.2, C38.2, MK2.2 (LR), MK2.3 (GND), R16.1, U3.1 (GND), U3.5 (SDO), U3.7 (GND), U9.1 (GND), U9.10 (GND), U9.12 (GND), U11.1 (SDO/SA0), U11.6 (GND), U11.7 (GND), U12.C1 (SDO), U12.C5 (GND), U12.E1 (GND), U12.E3 (GND), U13.2 (Feed/GND); also elsewhere on the board
unnamed: R14.2, U3.2 (CSB)
unnamed: C38.1, U9.14 (VCC_RF)
unnamed: R15.2, U9.6 (V_BCKP)

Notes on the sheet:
Audio
3ax Mag
Temp/Humidity/Pressure
GPS
6ax Accel/Gyro

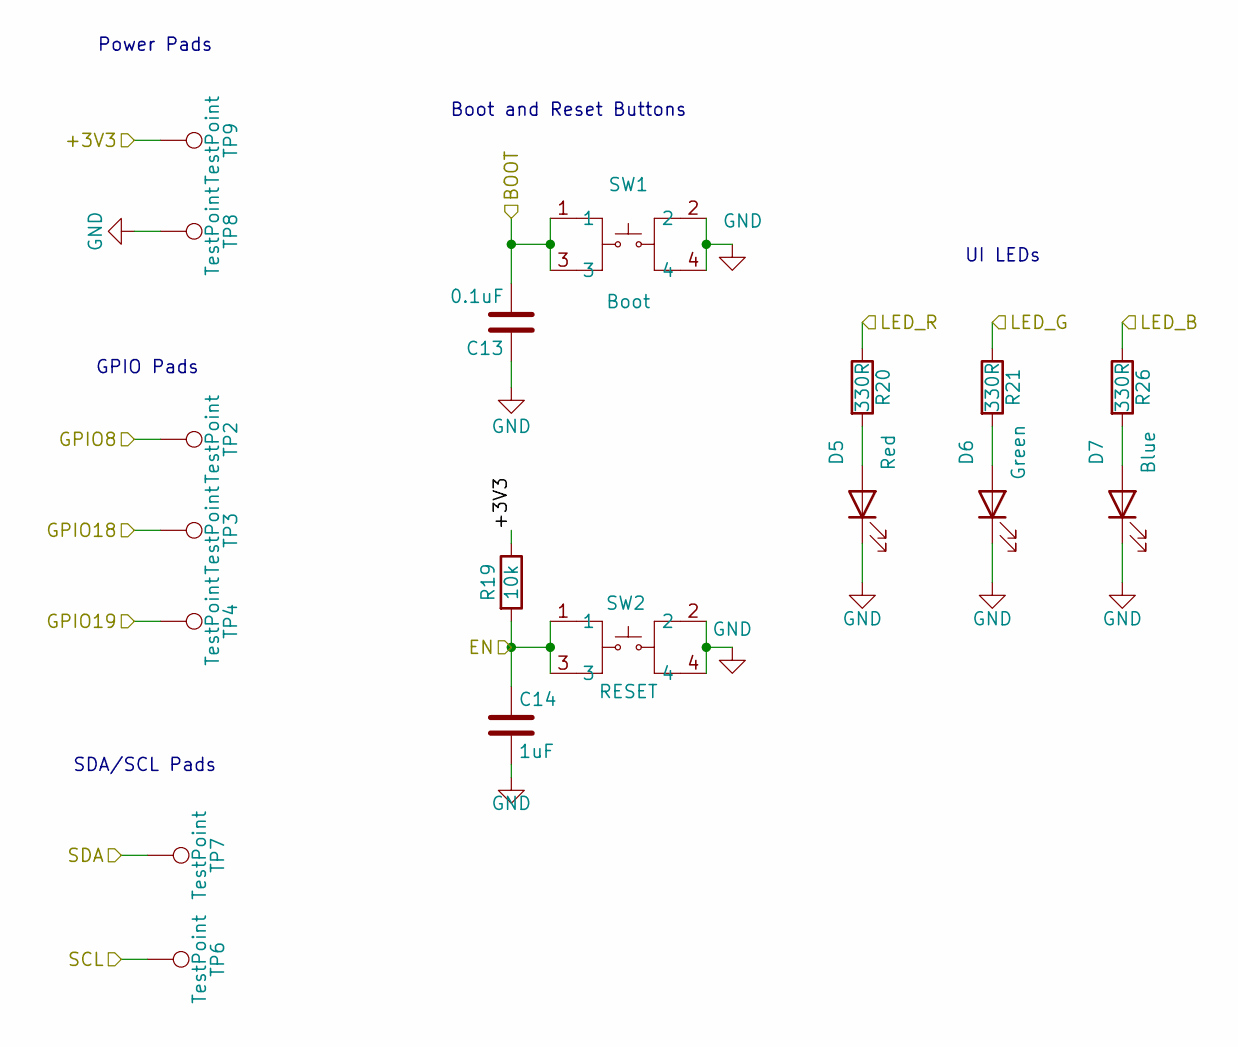
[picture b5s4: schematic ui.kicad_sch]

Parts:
C13: 0.1uF; C_0402_1005Metric
C14: 1uF; C_0402_1005Metric
D5: Red; LED_0402_1005Metric
D6: Green; LED_0402_1005Metric
D7: Blue; LED_0402_1005Metric
R19: 10k; R_0402_1005Metric
R20, R21, R26: 330R; R_0402_1005Metric
SW1: Boot; KEY-SMD_4P-L2.6-W1.6-P0.80-LS3.0; LCSC Part C358621
SW2: RESET; KEY-SMD_4P-L2.6-W1.6-P0.80-LS3.0; LCSC Part C358621
TP2, TP3, TP4, TP6, TP7, TP8, TP9: TestPoint; TestPoint_Pad_1.0x1.0mm

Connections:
+3V3: R19.1; also elsewhere on the board
/BOOT: C13.2, SW1.1, SW1.3; also elsewhere on the board
/EN: C14.1, R19.2, SW2.1, SW2.3; also elsewhere on the board
/LED_B: R26.1; also elsewhere on the board
/LED_G: R21.1; also elsewhere on the board
/LED_R: R20.1; also elsewhere on the board
GND: C13.1, C14.2, D5.1 (K), D6.1 (K), D7.1 (K), SW1.2, SW1.4, SW2.2, SW2.4, TP8.1; also elsewhere on the board
unnamed: D5.2 (A), R20.2
unnamed: D6.2 (A), R21.2
unnamed: D7.2 (A), R26.2

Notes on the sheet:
Boot and Reset Buttons
GPIO Pads
Power Pads
SDA/SCL Pads
UI LEDs
